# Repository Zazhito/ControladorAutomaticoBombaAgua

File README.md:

# ControladorAutomaticoBombaAgua
Diseño de controlador Analogico para bomba de agua

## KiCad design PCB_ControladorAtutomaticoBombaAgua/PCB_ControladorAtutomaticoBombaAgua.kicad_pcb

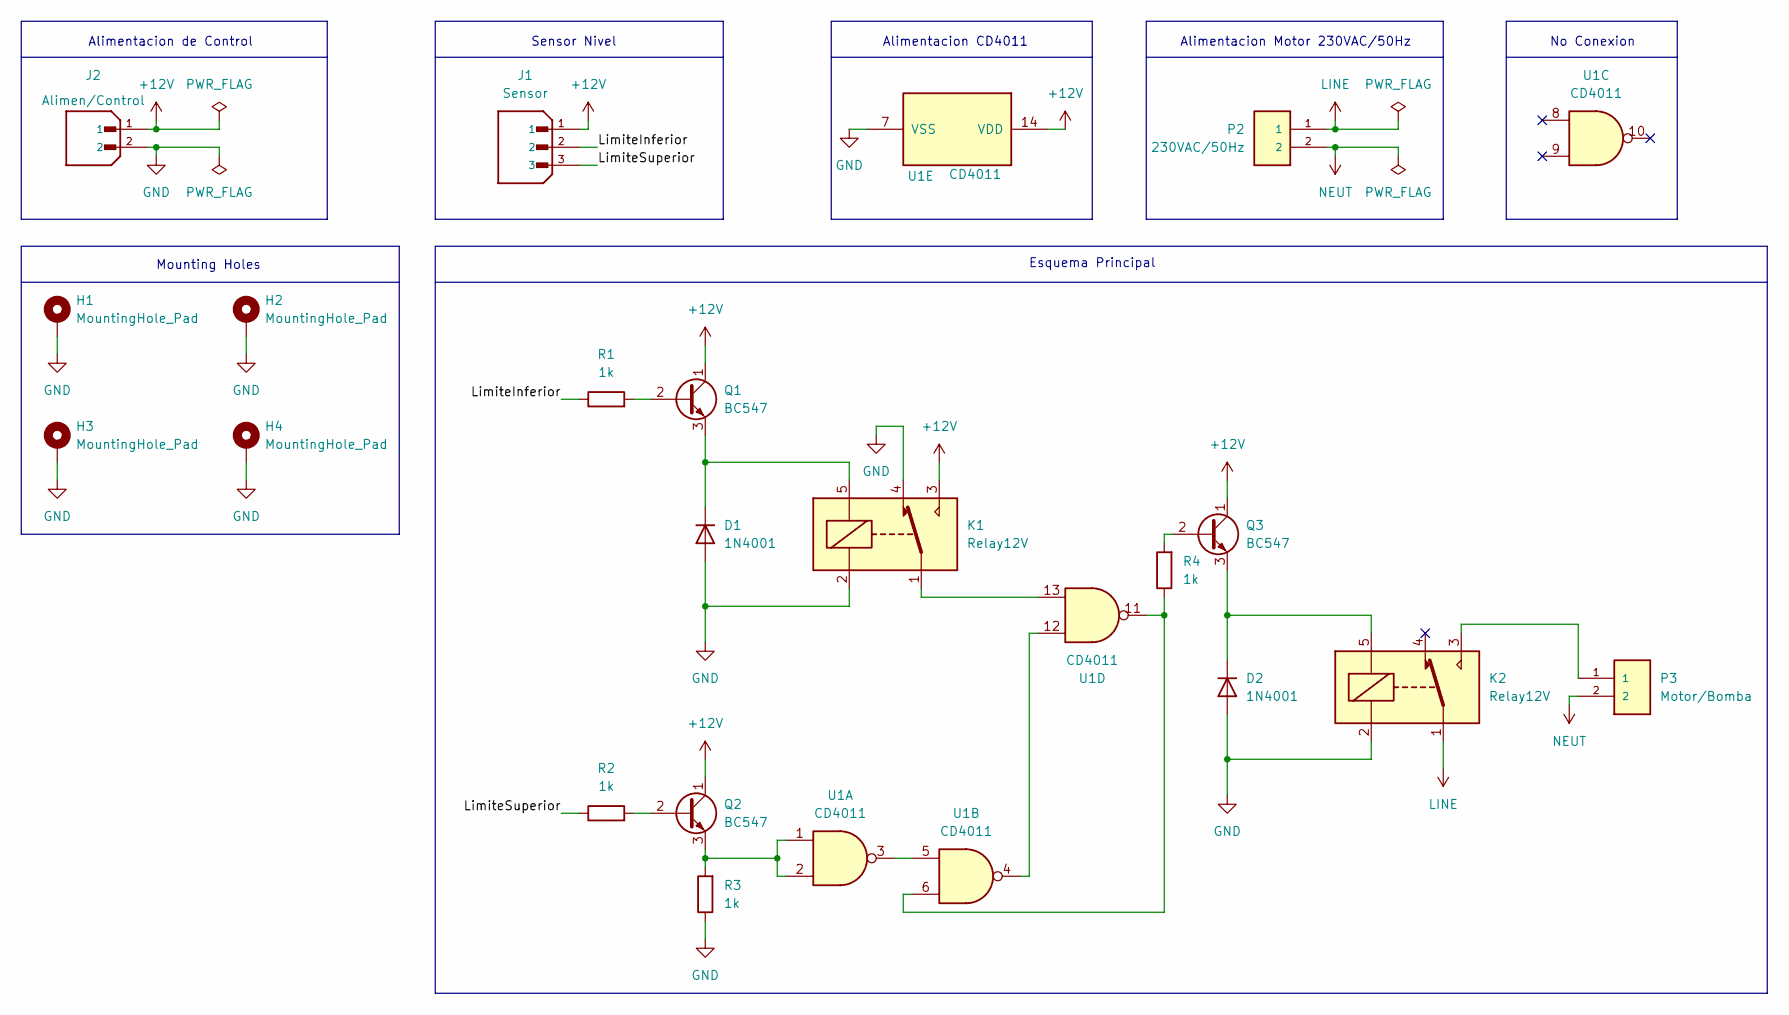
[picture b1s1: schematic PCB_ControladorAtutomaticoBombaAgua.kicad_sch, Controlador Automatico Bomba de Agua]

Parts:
D1, D2: 1N4001; D_DO-41_SOD81_P7.62mm_Horizontal
H1, H2, H3, H4: MountingHole_Pad; MountingHole_2.2mm_M2_Pad_Via
J1: Sensor; JST_B3B-XH-A; PARTREV 7/4/21
J2: Alimen/Control; JST_B2B-XH-A; PARTREV N/A
K1, K2: Relay12V; Relay_SPDT_SANYOU_SRD_Series_Form_C
P2: 230VAC/50Hz; BORNERA-2; PARTREV G3
P3: Motor/Bomba; BORNERA-2; PARTREV G3
Q1, Q2, Q3: BC547; TO-92_Inline
R1, R2, R3, R4: 1k; R_0805_2012Metric_Pad1.20x1.40mm_HandSolder
U1: CD4011; DIP-14_W7.62mm

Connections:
+12V: J1.1, J2.1, K1.3, Q1.1 (C), Q2.1 (C), Q3.1 (C), U1.14 (VDD)
/LimiteInferior: J1.2, R1.1
/LimiteSuperior: J1.3, R2.1
GND: D1.2 (A), D2.2 (A), H1.1, H2.1, H3.1, H4.1, J2.2, K1.2, K1.4, K2.2, R3.1, U1.7 (VSS)
LINE: K2.1, P2.1
NEUT: P2.2, P3.2
unnamed: D1.1 (K), K1.5, Q1.3 (E)
unnamed: D2.1 (K), K2.5, Q3.3 (E)
unnamed: K1.1, U1.13
unnamed: K2.3, P3.1
unnamed: Q1.2 (B), R1.2
unnamed: Q2.2 (B), R2.2
unnamed: Q2.3 (E), R3.2, U1.1, U1.2
unnamed: Q3.2 (B), R4.2
unnamed: R4.1, U1.6, U1.11
unnamed: U1.3, U1.5
unnamed: U1.4, U1.12

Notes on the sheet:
Sensor Nivel
Alimentacion de Control
Esquema Principal
Alimentacion Motor 230VAC/50Hz
Alimentacion CD4011
No Conexion
Mounting Holes

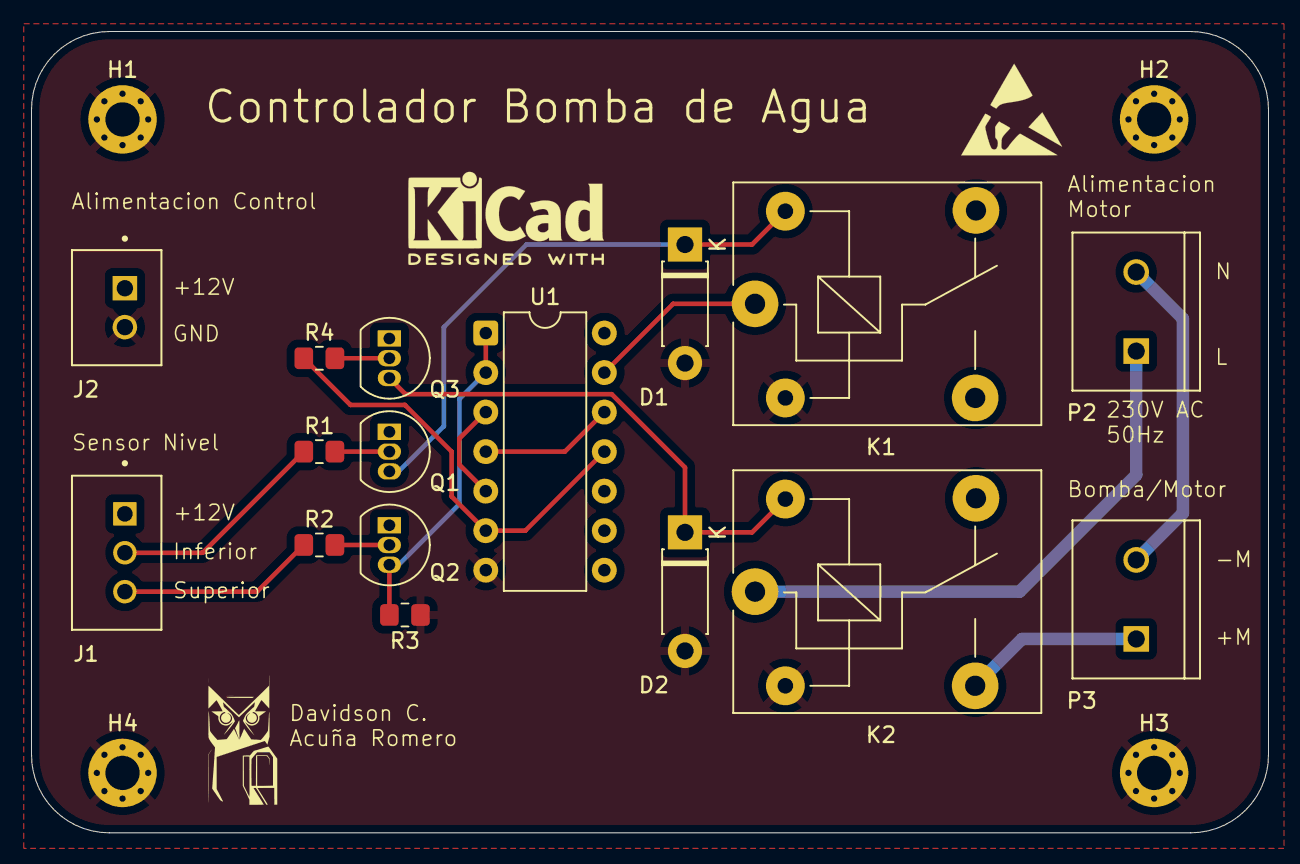
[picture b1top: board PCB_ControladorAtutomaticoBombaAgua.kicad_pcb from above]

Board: 2 copper layers, 79.5 x 51.5 mm, 20 parts (0 on the bottom side), 17 nets.

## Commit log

2025-05-19 Esquematico/PCB
    Esquemático completo, PCB en desarrollo
2025-05-22 Finalizado
    Diseño completado
2025-05-22 Finalizado
    Diseño Finalizado
